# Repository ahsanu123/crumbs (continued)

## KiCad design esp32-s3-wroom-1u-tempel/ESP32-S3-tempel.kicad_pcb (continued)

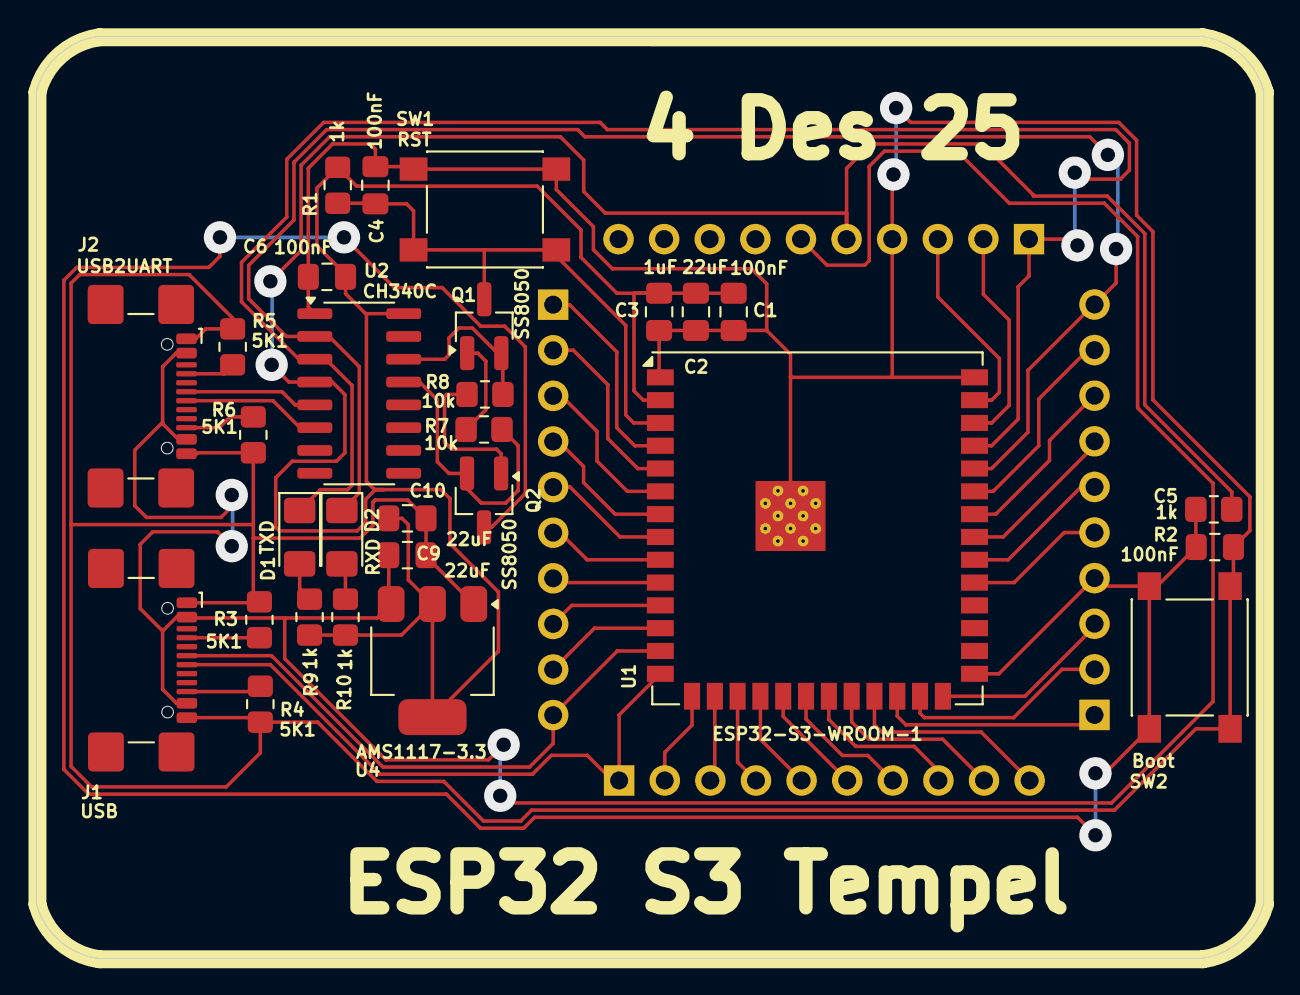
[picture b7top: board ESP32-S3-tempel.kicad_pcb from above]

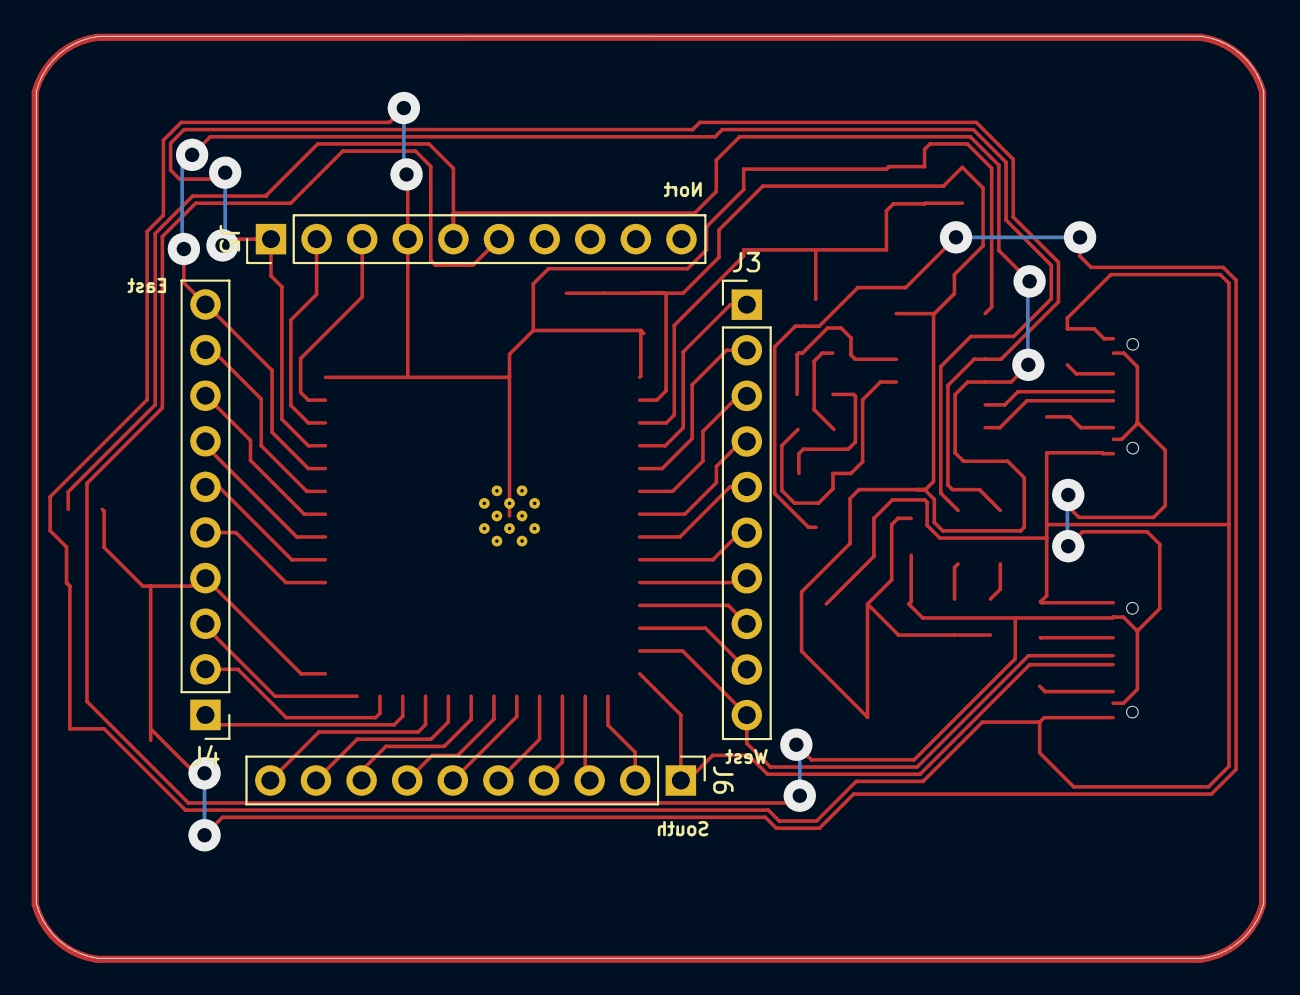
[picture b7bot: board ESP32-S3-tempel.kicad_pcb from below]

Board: 2 copper layers, 68.4 x 51.3 mm, 33 parts (4 on the bottom side), 49 nets.

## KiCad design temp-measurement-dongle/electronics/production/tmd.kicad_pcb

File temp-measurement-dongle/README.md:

# TMD V2

TMD - Temperature Measurement Dongle 

# Roadmap 

- add bluetooth support,
- create client application for desktop and android with slint,
- add plot feature to client application

## References 

- [plotters](https://github.com/plotters-rs/plotters/tree/master)
- [btelplug](https://github.com/deviceplug/btleplug)
- [slint plotters sample](https://github.com/slint-ui/slint/tree/master/examples/plotter)

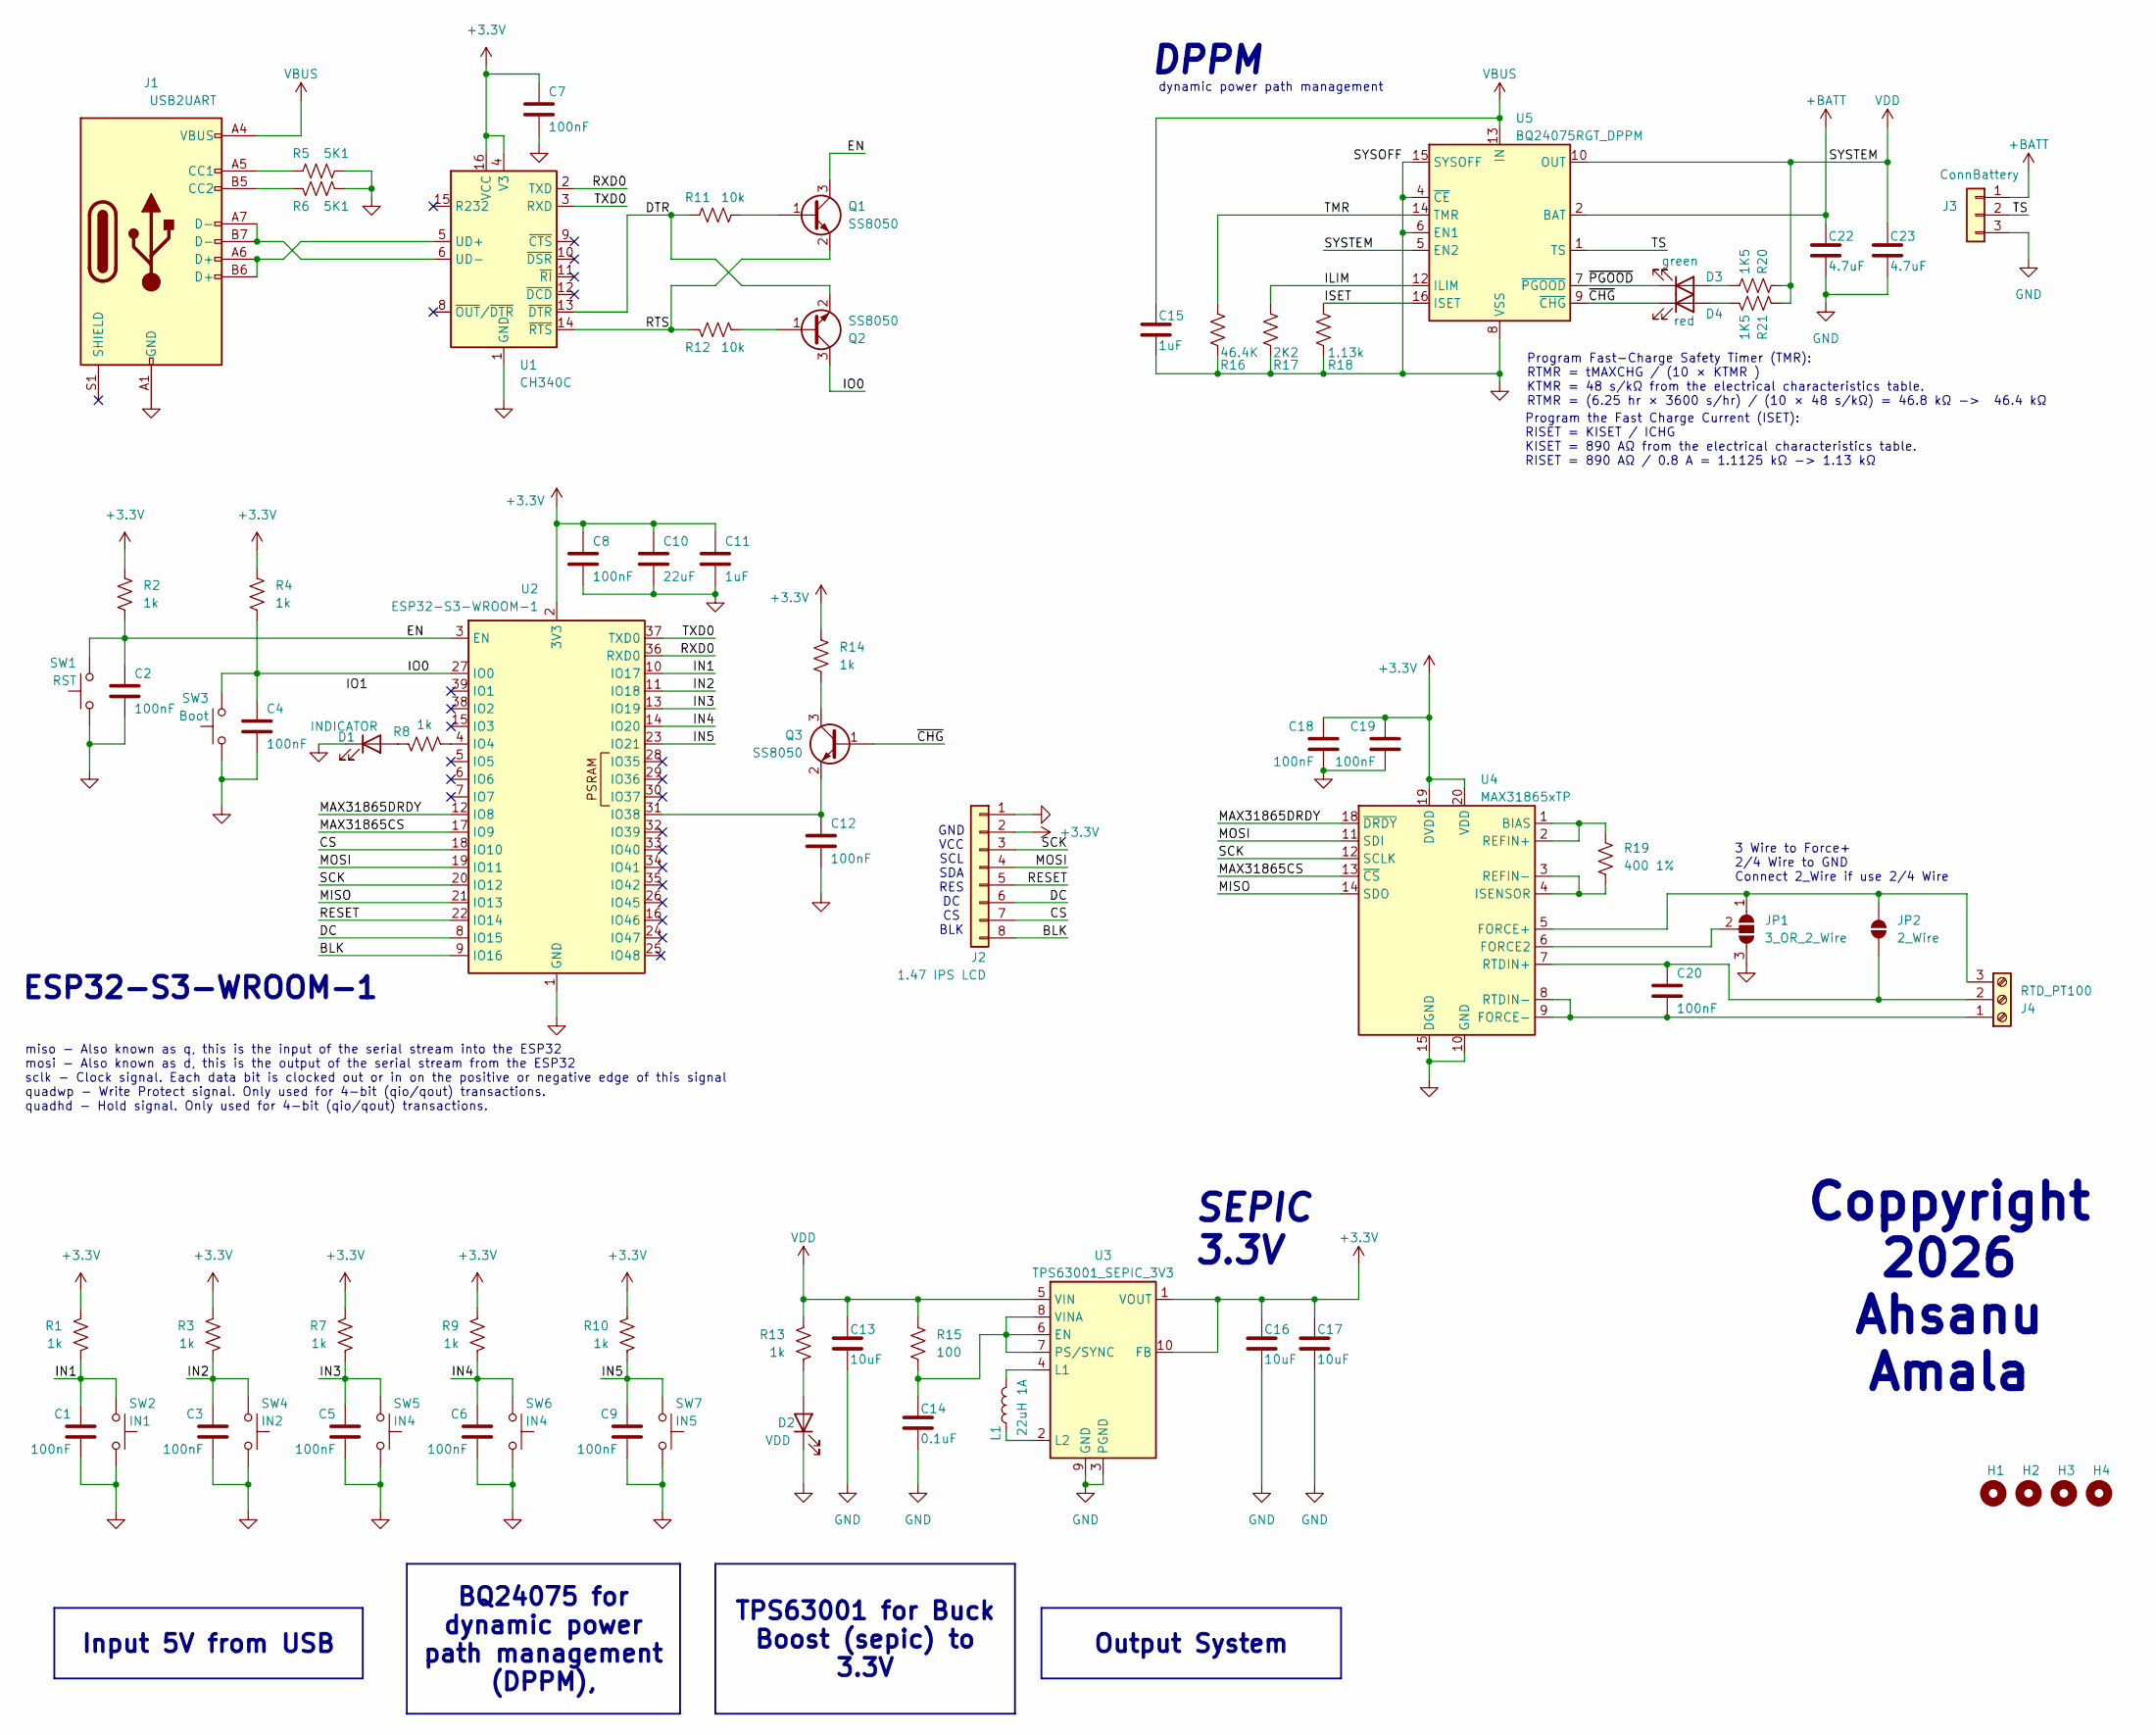
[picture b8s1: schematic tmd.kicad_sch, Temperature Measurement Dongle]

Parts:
C1, C2, C3, C4, C5, C6, C7, C8, C9, C12, C18, C19, C20: 100nF; C_0805_2012Metric_Pad1.18x1.45mm_HandSolder
C10: 22uF; C_0805_2012Metric_Pad1.18x1.45mm_HandSolder
C11, C15: 1uF; C_0805_2012Metric_Pad1.18x1.45mm_HandSolder
C13, C16, C17: 10uF; C_0805_2012Metric_Pad1.18x1.45mm_HandSolder
C14: 0.1uF; C_0805_2012Metric_Pad1.18x1.45mm_HandSolder
C22, C23: 4.7uF; C_0805_2012Metric_Pad1.18x1.45mm_HandSolder
D1: INDICATOR; LED_1206_3216Metric_Pad1.42x1.75mm_HandSolder
D2: VDD; LED_1206_3216Metric_Pad1.42x1.75mm_HandSolder
D3: green; LED_0805_2012Metric_Pad1.15x1.40mm_HandSolder
D4: red; LED_0805_2012Metric_Pad1.15x1.40mm_HandSolder
H1, H2, H3, H4: MountingHole; MountingHole_2mm
J1: USB2UART; USB_C_Receptacle_GCT_USB4110
J2: 1.47 IPS LCD; PinHeader_1x08_P2.54mm_Vertical
J3: ConnBattery; PinHeader_1x03_P2.54mm_Vertical
J4: RTD_PT100; TerminalBlock_Phoenix_PT-1,5-3-5.0-H_1x03_P5.00mm_Horizontal
JP1: 3_OR_2_Wire; SolderJumper-3_P1.3mm_Open_RoundedPad1.0x1.5mm
JP2: 2_Wire; SolderJumper-2_P1.3mm_Open_TrianglePad1.0x1.5mm
L1: 22uH 1A; L_Bourns_SRP7028A_7.3x6.6mm
Q1, Q2, Q3: SS8050; SOT-23_Handsoldering
R1, R2, R3, R4, R7, R8, R9, R10, R13, R14: 1k; R_0805_2012Metric_Pad1.20x1.40mm_HandSolder
R5, R6: 5K1; R_0805_2012Metric_Pad1.20x1.40mm_HandSolder
R11, R12: 10k; R_0805_2012Metric_Pad1.20x1.40mm_HandSolder
R15: 100; R_0805_2012Metric_Pad1.20x1.40mm_HandSolder
R16: 46.4K; R_0805_2012Metric_Pad1.20x1.40mm_HandSolder
R17: 2K2; R_0805_2012Metric_Pad1.20x1.40mm_HandSolder
R18: 1.13k; R_0805_2012Metric_Pad1.20x1.40mm_HandSolder
R19: 400 1%; R_0805_2012Metric_Pad1.20x1.40mm_HandSolder
R20, R21: 1K5; R_0805_2012Metric_Pad1.20x1.40mm_HandSolder
SW1: RST; SW_SPST_PTS810
SW2: IN1; SW_SPST_Omron_B3FS-100xP
SW3: Boot; SW_SPST_PTS810
SW4: IN2; SW_SPST_Omron_B3FS-100xP
SW5, SW6: IN4; SW_SPST_Omron_B3FS-100xP
SW7: IN5; SW_SPST_Omron_B3FS-100xP
U1: CH340C; SOIC-16_3.9x9.9mm_P1.27mm
U2: ESP32-S3-WROOM-1
U3: TPS63001_SEPIC_3V3; Texas_DRC0010J_ThermalVias
U4: MAX31865xTP; TQFN-20-1EP_5x5mm_P0.65mm_EP3.25x3.25mm
U5: BQ24075RGT_DPPM; VQFN-16-1EP_3x3mm_P0.5mm_EP1.6x1.6mm

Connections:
+3.3V: C7.1, C8.1, C10.1, C11.1, C16.1, C17.1, C18.1, C19.1, J2.2, R1.1, R2.1, R3.1, R4.1, R7.1, R9.1, R10.1, R14.1, U1.4 (V3), U1.16 (VCC), U2.2 (3V3), U3.1 (VOUT), U3.10 (FB), U4.19 (DVDD), U4.20 (VDD)
+BATT: C22.1, J3.1, U5.2 (BAT), U5.3 (BAT)
/BLK: J2.8, U2.9 (IO16)
/CS: J2.7, U2.18 (IO10)
/DC: J2.6, U2.8 (IO15)
/DTR: Q2.2 (E), R11.2, U1.13 (~DTR)
/EN: C2.1, Q1.3 (C), R2.2, SW1.2, U2.3 (EN)
/ILIM: R17.1, U5.12 (ILIM)
/IN1: C1.1, R1.2, SW2.2, U2.10 (IO17)
/IN2: C3.1, R3.2, SW4.2, U2.11 (IO18)
/IN3: C5.1, R7.2, SW5.2, U2.13 (IO19)
/IN4: C6.1, R9.2, SW6.2, U2.14 (IO20)
/IN5: C9.1, R10.2, SW7.2, U2.23 (IO21)
/IO0: C4.1, Q2.3 (C), R4.2, SW3.2, U2.27 (IO0)
/ISET: R18.1, U5.16 (ISET)
/MAX31865CS: U2.17 (IO9), U4.13 (~CS)
/MAX31865DRDY: U2.12 (IO8), U4.18 (~DRDY)
/MISO: U2.21 (IO13), U4.14 (SDO)
/MOSI: J2.4, U2.19 (IO11), U4.11 (SDI)
/RESET: J2.5, U2.22 (IO14)
/RTS: Q1.2 (E), R12.2, U1.14 (~RTS)
/RXD0: U1.2 (TXD), U2.36 (RXD0)
/SCK: J2.3, U2.20 (IO12), U4.12 (SCLK)
/TMR: R16.1, U5.14 (TMR)
/TS: J3.2, U5.1 (TS)
/TXD0: U1.3 (RXD), U2.37 (TXD0)
/~CHG: D4.1 (K), Q3.1 (B), U5.9 (~CHG)
/~PGOOD: D3.1 (K), U5.7 (~PGOOD)
GND: C1.2, C2.2, C3.2, C4.2, C5.2, C6.2, C7.2, C8.2, C9.2, C10.2, C11.2, C12.2, C13.2, C14.2, C15.2, C16.2, C17.2, C18.2, C19.2, C22.2, C23.2, D1.1 (K), D2.1 (K), J1.A1 (GND), J1.A12 (GND), J1.B1 (GND), J1.B12 (GND), J2.1, J3.3, JP1.3 (B), R5.1, R6.1, R16.2, R17.2, R18.2, SW1.1, SW2.1, SW3.1, SW4.1, SW5.1, SW6.1, SW7.1, U1.1 (GND), U2.1 (GND), U2.40 (GND), U2.41 (GND), U3.3 (PGND), U3.9 (GND), U3.11 (PGND), U4.10 (GND), U4.15 (DGND), U4.16 (GND), U4.21 (GND), U5.4 (~CE), U5.6 (EN1), U5.8 (VSS), U5.15 (SYSOFF), U5.17 (VSS)
unnamed: D1.2 (A), R8.1
unnamed: D2.2 (A), R13.2
unnamed: D3.2 (A), R20.1
unnamed: D4.2 (A), R21.1
unnamed: J1.A5 (CC1), R5.2
unnamed: J1.B5 (CC2), R6.2
unnamed: C20.2, J4.1, U4.8 (RTDIN-), U4.9 (FORCE-)
unnamed: C20.1, J4.2, JP2.1 (A), U4.7 (RTDIN+)
unnamed: J4.3, JP1.1 (A), JP2.2 (B), U4.5 (FORCE+)
unnamed: JP1.2 (C), U4.6 (FORCE2)
unnamed: Q1.1 (B), R11.1
unnamed: Q2.1 (B), R12.1
unnamed: Q3.3 (C), R14.2
unnamed: C12.1, Q3.2 (E), U2.31 (IO38)
unnamed: J1.A6 (D+), J1.B6 (D+), U1.5 (UD+)
unnamed: J1.A7 (D-), J1.B7 (D-), U1.6 (UD-)
unnamed: R8.2, U2.4 (IO4)
unnamed: C14.1, R15.2, U3.6 (EN), U3.7 (PS/SYNC), U3.8 (VINA)
unnamed: L1.2, U3.4 (L1)
unnamed: L1.1, U3.2 (L2)
unnamed: R19.1, U4.1 (BIAS), U4.2 (REFIN+)
unnamed: R19.2, U4.3 (REFIN-), U4.4 (ISENSOR)
VBUS: C15.1, J1.A4 (VBUS), J1.A9 (VBUS), J1.B4 (VBUS), J1.B9 (VBUS), U5.13 (IN)
VDD: C13.1, C23.1, R13.1, R15.1, R20.2, R21.2, U3.5 (VIN), U5.5 (EN2), U5.10 (OUT), U5.11 (OUT)

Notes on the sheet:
dynamic power path management
GND VCC SCL SDA RES DC CS BLK
miso - Also known as q, this is the input of the serial stream into the ESP32 mosi - Also known as d, this is the output of the serial stream from the ESP32 sclk - Clock signal. Each data bit is clocked out or in on the positive or negative edge of this signal quadwp - Write Protect signal. Only us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
ESP32-S3-WROOM-1
Program the Fast Charge Current (ISET): RISET = KISET / ICHG KISET = 890 AΩ from the electrical characteristics table. RISET = 890 AΩ / 0.8 A = 1.1125 kΩ -> 1.13 kΩ
DPPM
3 Wire to Force+ 2/4 Wire to GND Connect 2_Wire if use 2/4 Wire
SEPIC 3.3V
Program Fast-Charge Safety Timer (TMR): RTMR = tMAXCHG / (10 × KTMR ) KTMR = 48 s/kΩ from the electrical characteristics table. RTMR = (6.25 hr × 3600 s/hr) / (10 × 48 s/kΩ) = 46.8 kΩ -> 46.4 kΩ
Output System
TPS63001 for Buck Boost (sepic) to 3.3V
Coppyright 2026 Ahsanu Amala
Input 5V from USB
BQ24075 for dynamic power path management (DPPM),

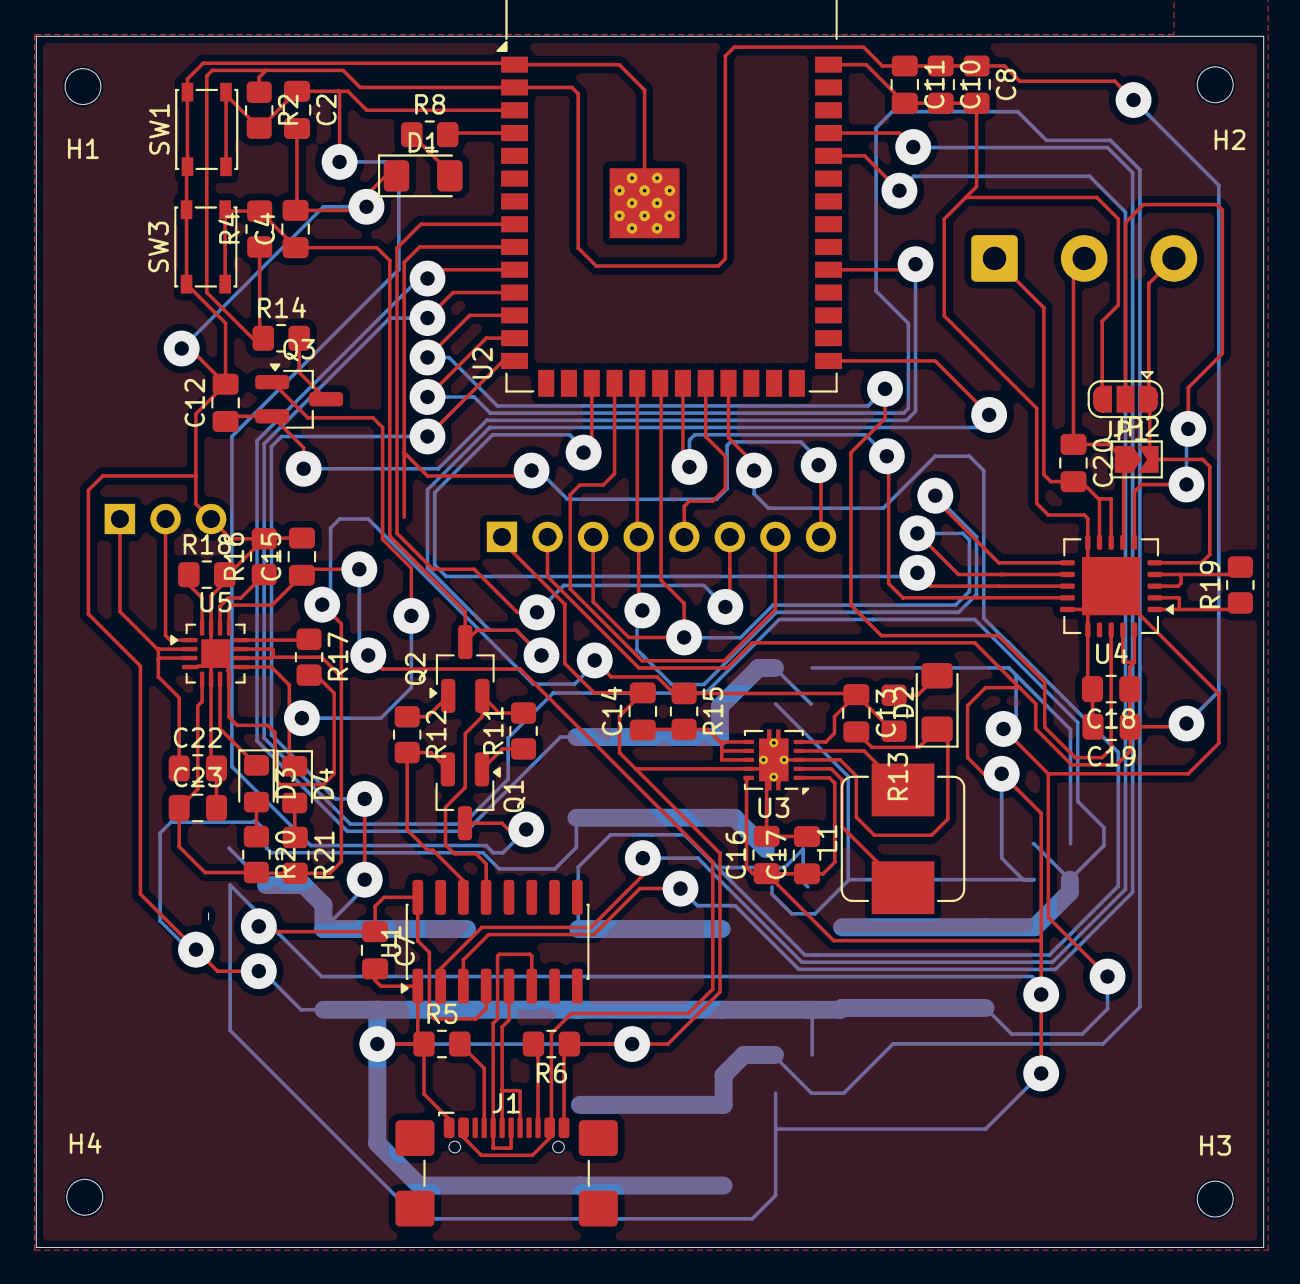
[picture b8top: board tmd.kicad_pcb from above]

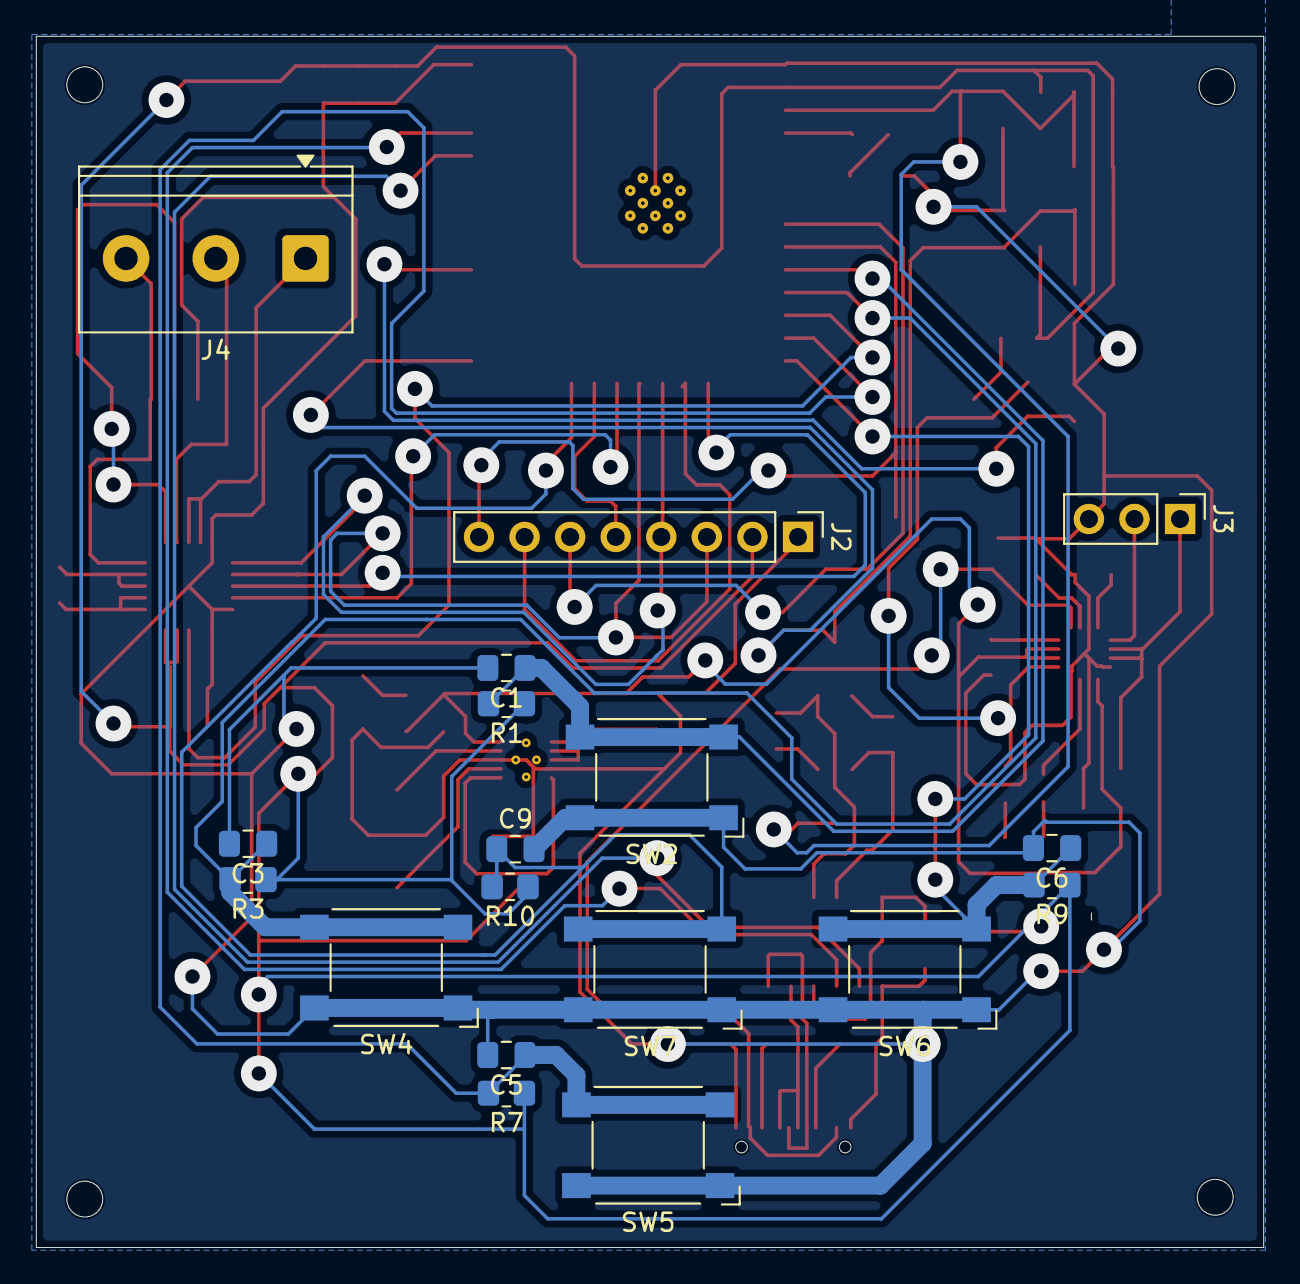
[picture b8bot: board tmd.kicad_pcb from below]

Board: 2 copper layers, 68.4 x 67.5 mm, 73 parts (18 on the bottom side), 53 nets.

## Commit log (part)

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2024-06-26 add License and readme
2024-06-26 finish route
2024-06-27 finish route and generate pdf
2024-06-28 update clearance
2024-06-28 add schematic svg
2024-06-28 add background to svg
2024-06-30 [30-6-1202] Crumbs TMC2208 Init Commit
2024-06-30 [30-6-1209] Crumbs MCP23017 Init Commit
2024-06-30 change crumbs TMC2208 Kicad Root Directory
2024-07-02 update name to use crumbs
2024-07-09 update crumbs595
2024-12-08 [12-09-2024] TB-03 - Add Schematic and several documentation
    Update README.md
2024-12-09 [12-09-2005] TB-03 Finish Schematic, need recheck
    add readme
    Update README.md
2024-12-10 [12-10-2018] TB-03 Finish Component Layout, Need to Route And Recheck
    Update README.md
2024-12-11 [12-11-2017] TB-03 Finish Routing, Need Recheck Board and Schematic
2024-12-12 [12-12-2151] create logo and arrange silkscreen
    Update README.md
2025-01-15 [01-15-1749] add black magic probe to crumbs
    add black magic probe
    nit document
    update schematic
2025-01-16 [01-16-1532] very little schematic update
2025-01-17 [01-17-1807] remove black magic into new repo
2025-04-14 [04-14-1717] Create Hokushime DB9 to RS232
    Update README.md
    add external library
2025-04-15 [04-15-0604] renaming hokshime db9 to rs232, to hokushime hiroshe usb to rs232
    nit
    Update README.md
    Update README.md
2025-04-15 [04-15-0702] change to use ic 93CXX
    nit
2025-04-15 [04-15-2111] finish first schematic
    Update README.md
    Update README.md
2025-04-21 [04-22-0550] Hokushime create pcb and basic layout
    Update README.md
2025-04-22 [04-22-1840] thing about vias making
2025-04-24 [04-24-1904] pcb routing finished
2025-05-16 [05-16-1248] change vias to 0.8 mm for manual driling
2025-05-18 [05-18-0917] re-routing and flip component
2025-05-18 [05-18-1145] make manufacturing file, look good, but drill is missing, need to buy one
2025-05-25 [05-25-1346] make manufacturing file
2025-06-11 [06-12-0518] add log to readme
    nit license year
2025-06-13 [06-13-0759] change package to correct package SSOP and 32QFP, also make manufacture step doc
2025-06-14 change image and finish first prototype soldering
2025-06-19 [06-19-2121] add device descriptor, vid, and pid dump
2025-06-24 [06-24-2107] Create WiringGuide.md
2025-11-03 feat: progress routing tempel
2025-11-03 feat: finish routing
    Update README.md
2025-11-04 feat: add panelization
2025-11-06 feat: tempel rp2350 route revision 2
2025-11-08 chore: update after first prototype created
2025-11-14 feat: finish rp2350-dev-board schematic
2025-11-25 feat: progress on routing tempel rp2350a dev board
2025-12-04 feat: add esp32-s3 tempel
2025-12-04 feat: finish routing and tidyng silkscreen
2025-12-04 feat: use tempel to simplify design
2025-12-31 feat: add esp32-s3-tempel schematic
    Update README.md
2025-12-31 feat: duplicate wroom 1u to wroom 1 (built in antenas)
    n
2026-02-15 chore: remove several un-needed file and folder
2026-02-16 feat: make esp32-s3-wroom-1 temple route more ticker
2026-02-18 feat: create esp32-s3-proto-dev
2026-03-07 feat: create double layer poc with esp32 s3 wroom 1
2026-03-16 feat: add temp-measurement-dongle
2026-03-16 fix: swapped spid(mosi) in proto-double-layer
2026-03-17 feat: finish schematic of temperature-measurement-dongle
2026-03-17 feat: finish 2 layer routing temperature measurement dongle
2026-03-27 chore: exclude from simulation
2026-03-28 feat: rearranging front value
2026-03-30 feat: add tmc2209-module project
2026-03-30 feat: update route, flipped lcd screen
2026-04-07 feat: initialized crumbs drv8323 and finish schematic
2026-04-07 feat: initialized crumbs lm5145
2026-04-07 feat: first iteration on drv8323 schematic
2026-04-08 feat: assign correct footprint
2026-04-10 feat: drv8323 finish routing
2026-04-11 feat: copying carga firmware v1 to tmd firmware
2026-04-11 feat: quick dirty create ui design
2026-04-11 feat: create structure to handle ui state
2026-04-11 feat: create max31865 reading pt100 implementation
2026-04-12 feat: create max31865 reading poc (work)
2026-04-12 feat: implement effect handler for every store properties
2026-04-12 chore: use spi2 for lcd, and spi3 for max31865
2026-04-12 feat: ui and max31865 is work, but spi mode is not compitable for those two
2026-04-15 feat: move app_weak inside effect instead of manually passing from store
2026-04-16 feat: use st7735s with mode 1 is working
2026-04-16 feat: add ili9341, but mode 1/3 is not fully worked
2026-04-17 chore: change max31865 delay to 100ms
2026-04-17 feat: add hello_world bin, to test bq24075 DPPM
2026-04-17 feat: change ui design to match st8835 small dimension
2026-04-17 feat: add embed font size with set_var
2026-04-17 feat: add crumbs-rp2350 to test hstx
2026-04-21 feat: tweaking tmd style
2026-04-21 feat: tmd, add max17048 and bq27220
2026-04-21 feat(tmd): update schematic to use fuel gauge bq27421
2026-04-22 chore: move libraries to mkl
2026-04-22 feat: add mkl as libraries submodule
2026-04-24 feat(regi): init regi the explorer
2026-04-24 feat(regi): defining form structure and test for performance (it too slow)
2026-04-24 feat(regi): delegate uniform component creation and state to custom component and buffer
2026-04-26 feat(regi): add registers and combined register component
2026-04-26 feat(regi): add drag n drop to combined register
2026-04-26 feat(regi): start to create interpreter register editor
2026-04-28 feat(regi): start to add mathjs functionality to calculate formula from mock value
2026-04-28 feat(tmd): add lcd jumper
2026-05-05 feat(rp2350-devboard): copying tmc2209 and rp2350a-tempel into rp2350a devboard
2026-05-06 feat(regi): init tui project
2026-05-09 feat(regi): make several update
2026-05-09 feat(regi): fix ordered logic
2026-05-10 feat(regi): add mock and default value input
2026-05-10 chore(regi): remove uneeded file
2026-05-18 feat(tmd): add error from max31865 reading result
2026-05-19 feat(regi): init repl
2026-05-19 feat(regi): basic flatbuffer structure on repl
2026-05-21 feat(regi): finished rough routing
2026-05-23 feat(regi): attempt to generate gcode with pcb2gcode but flatcam feel better for this case
2026-06-16 feat(rp2350-dev-board): routing phase 1
2026-06-20 miolari initialization
2026-06-21 miolari finish routing
2026-06-21 start miolari rp2350
2026-06-23 remove crumbs rp2350a
2026-06-23 renaming tmc2209 to miolari tmc2209
2026-06-23 miolari rp2350a routing phase2
2026-06-27 miolari rp2350a routing phase3
2026-06-27 add idc connector to miolari tmc2209
2026-06-30 finish un-tidy miolari tmc2209
2026-06-30 copying cs1237 from tmc2209 project
2026-06-30 create miolari hx711
